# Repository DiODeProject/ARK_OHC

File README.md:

# ARK - Overhead Controller of Sheffield Robotics

Here we provide the Eagle files (schematics, layouts and gerbers) for the implementation of the new Overhead Controller (OHC) for the Kilobots. 

The bootloader for the microcontroller (Atmega328, 16MHZ) is the same as the Arduino Pro Mini and can be found here: https://github.com/arduino/Arduino/tree/master/hardware/arduino/avr/bootloaders/atmega 

The software for the microcontroller can be found here: https://github.com/acornejo/kilolib. 
Because we use 6 IR LED boards instead of 1, in file `ohc.c` we need to change line 33 to `#define ir_mask 0b00111111 | PORTB`. And then compile on the terminal as `make arduino-ohc-16mhz`.

## Citation
If you make use of or extend this design please cite:

* Nikolaidis, E., Sabo, C., Marshall, J. A. R., Reina, A. (2017) Characterisation and upgrade of the communication between overhead controllers and Kilobots. doi: [10.15131/shef.data.4990910.v2](https://figshare.com/articles/Characterisation_and_upgrade_of_the_communication_between_overhead_controllers_and_Kilobots/4990910)

## See Also
* [KilobotArena](https://github.com/DiODeProject/KilobotArena)
* [Kilobot Wiki](http://diode.group.shef.ac.uk/kilobots/index.php/Kilobots)

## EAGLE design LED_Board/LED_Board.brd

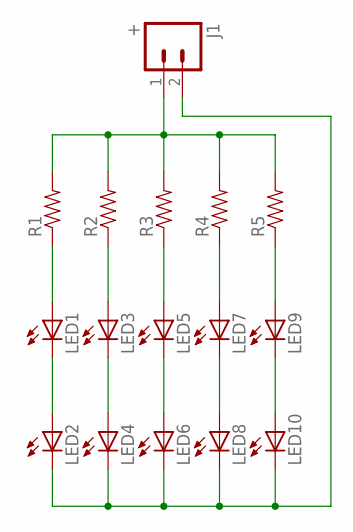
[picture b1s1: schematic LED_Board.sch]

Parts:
J1: +; 1X02_LOCK
LED1, LED2, LED3, LED4, LED5, LED6, LED7, LED8, LED9, LED10: LED5MM
R1, R2, R3, R4, R5: RESISTOR1206; 1206

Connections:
GND: J1.2, LED2.K (C), LED4.K (C), LED6.K (C), LED8.K (C), LED10.K (C)
unnamed: J1.1, R1.2, R2.2, R3.2, R4.2, R5.2
unnamed: LED9.A, R5.1
unnamed: LED7.A, R4.1
unnamed: LED5.A, R3.1
unnamed: LED3.A, R2.1
unnamed: LED1.A, R1.1
unnamed: LED1.K (C), LED2.A
unnamed: LED3.K (C), LED4.A
unnamed: LED5.K (C), LED6.A
unnamed: LED7.K (C), LED8.A
unnamed: LED9.K (C), LED10.A

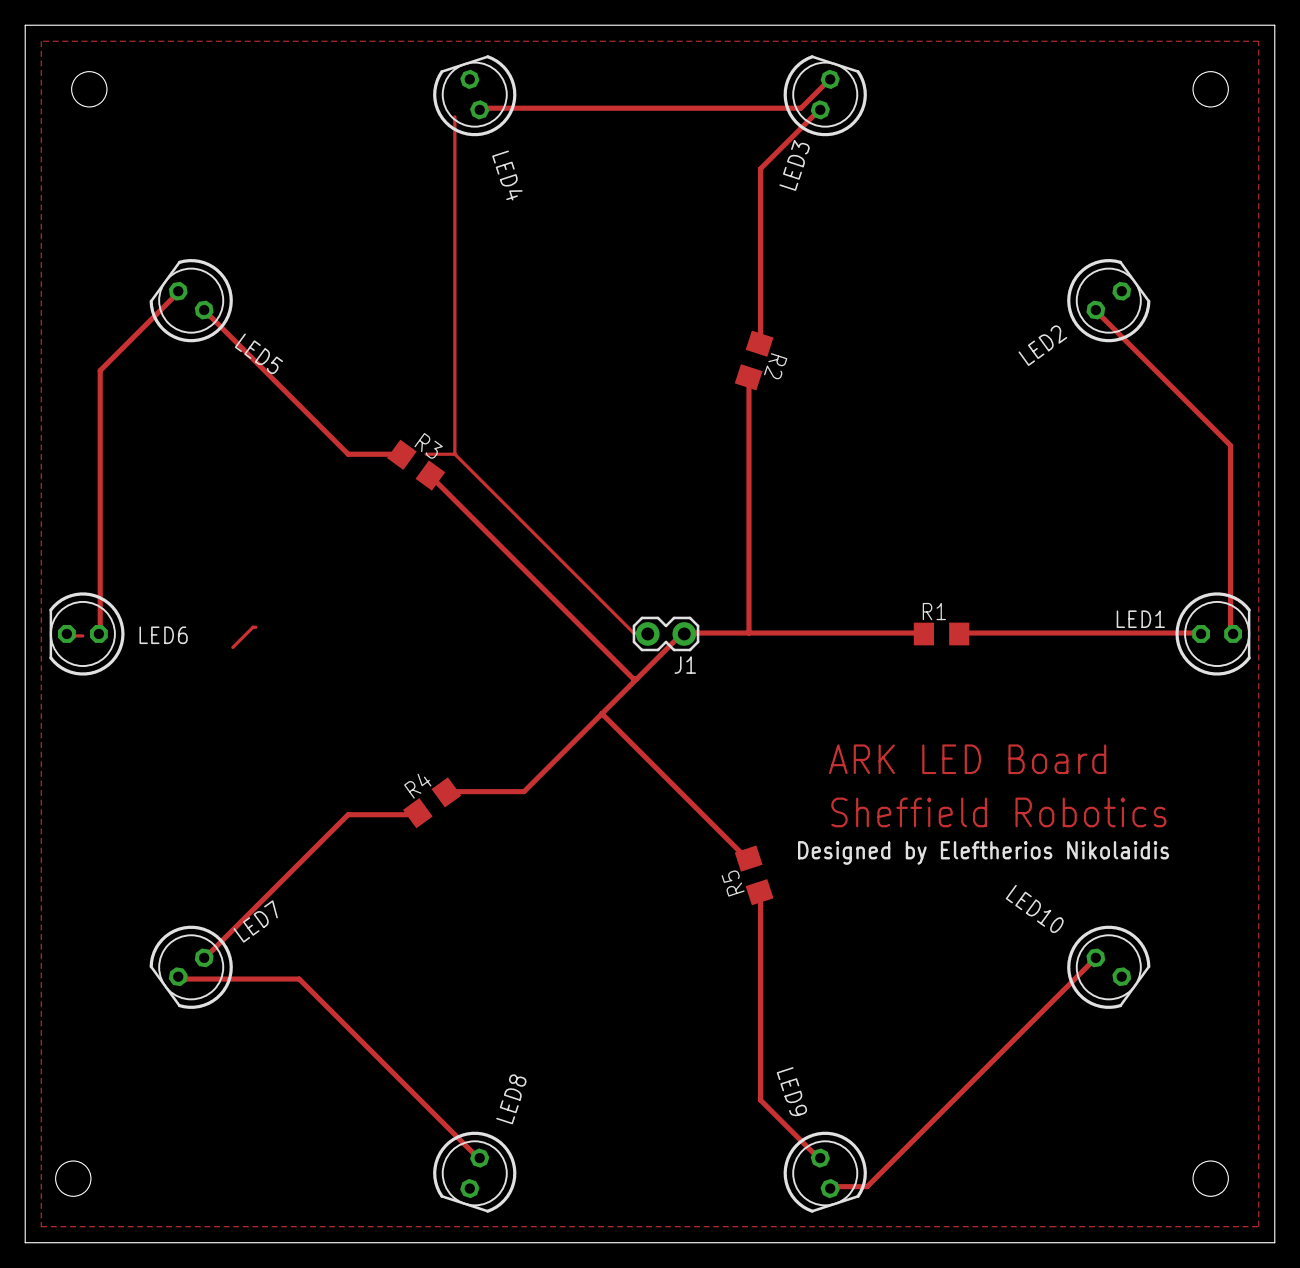
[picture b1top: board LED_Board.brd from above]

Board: 2 copper layers, 99.1 x 96.5 mm, 16 parts (0 on the bottom side), 12 nets.

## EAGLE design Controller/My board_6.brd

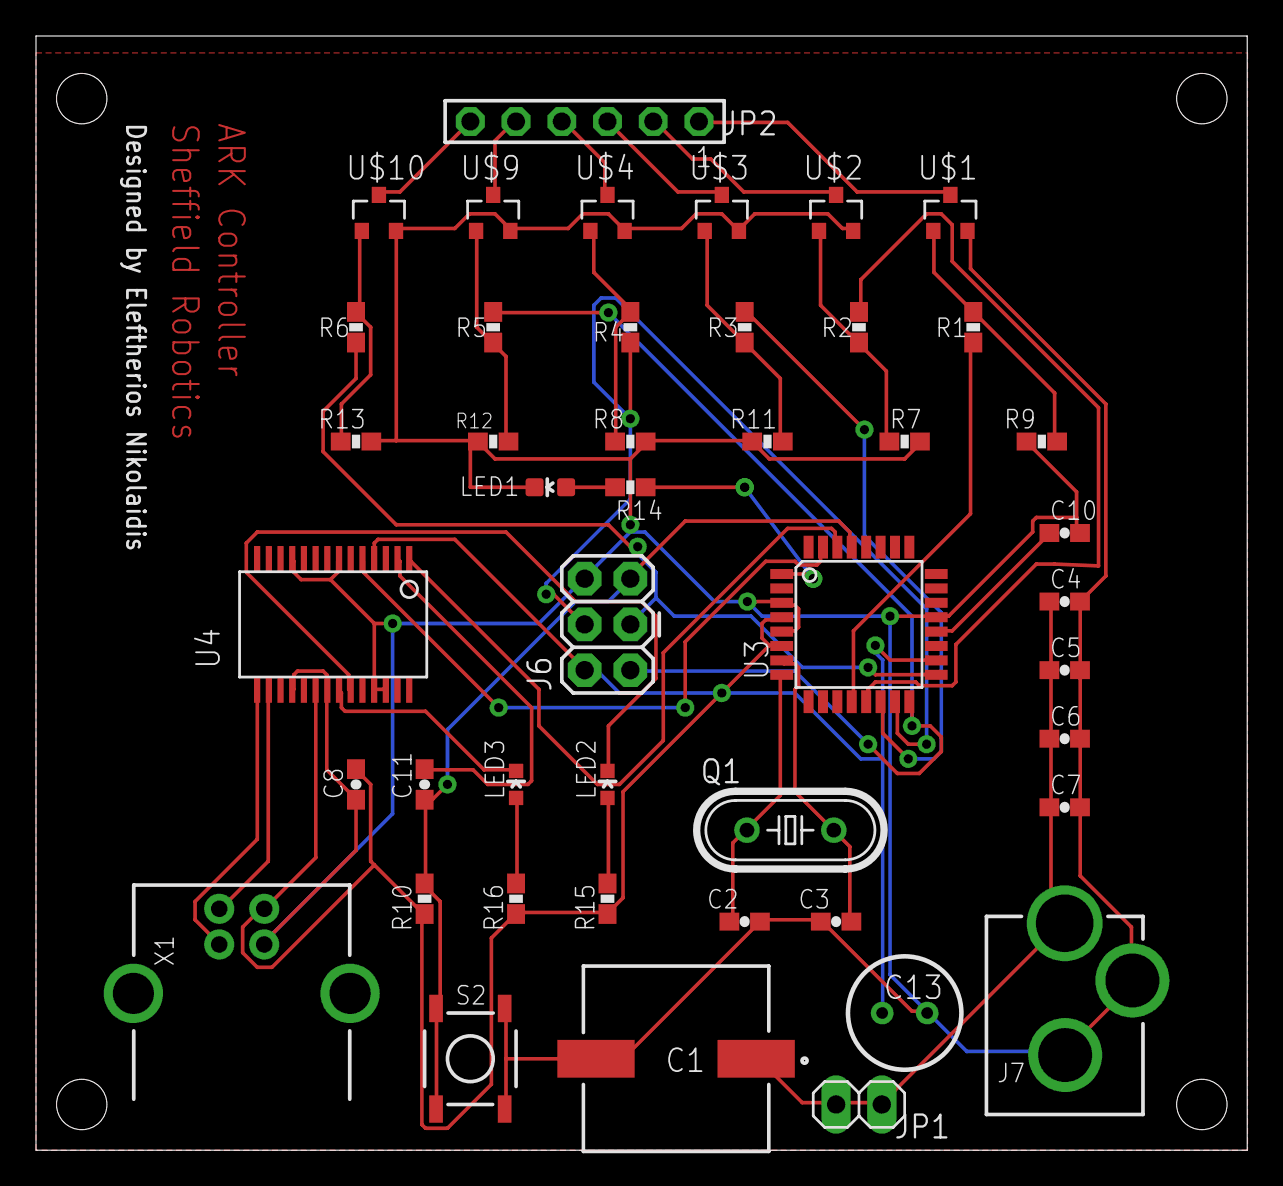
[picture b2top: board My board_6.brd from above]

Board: 2 copper layers, 67.3 x 61.9 mm, 45 parts (0 on the bottom side), 36 nets.

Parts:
C1: EEEFK1E471P; ALUMINUM-ELECTROLYTIC-CAPACITO
C2, C3: 22pf; 0603-CAP
C4, C5, C6, C7, C8, C10, C11: 0.1uF; 0603-CAP
C13: 10uF; ECEA1HKS100B
J6: ICSP; 2X3
J7: POWER_JACK; POWER_JACK_PTH_LOCK
JP1: 1X02
JP2: TSW-106-02-S-S
LED1, LED3: Green; LED-0603
LED2: Red; LED-0603
Q1: HC49/S
R1, R2, R3, R4, R5, R6: 100; 0603-RES
R7, R8, R9, R11, R12, R13: 47k; 0603-RES
R10: 10K; 0603-RES
R14, R15, R16: 1K; 0603-RES
S2: Reset; TACTILE-SWITCH-SMD-ALT01
U3: ATMEGA328; TQFP32-08
U4: FT232RL; SSOP28DB
U$1, U$2, U$3, U$4, U$9: SOT23-3
U$10: N-CHANNEL-MOSFETs-BSS138; SOT23-3
X1: USB-B; USB-B-PTH

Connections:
AREF: C10.2, U3.20
DTR1: C11.2, U4.2
GND: C1.2, C2.2, C3.2, C4.2, C5.2, C6.2, C7.2, C8.2, C10.1, C13.2, J6.6, J7.GND, J7.GNDBREAK, LED1.C, R7.2, R8.2, R9.2, R11.2, R12.2, R13.2, S2.1, S2.2, U3.3, U3.5, U3.21, U4.7, U4.11, U4.18, U4.21, U4.25, U4.26, U$1.2, U$2.2, U$3.2, U$4.2, U$9.2, U$10.2, X1.GND
unnamed: JP2.5, U$9.3
unnamed: JP2.6, U$10.3
unnamed: R3.2, U3.14
unnamed: R2.1, R7.1, U$2.1
unnamed: R3.1, R11.1, U$3.1
unnamed: R1.1, R9.1, U$1.1
unnamed: R4.1, R8.1, U$4.1
unnamed: R5.1, R12.1, U$9.1
unnamed: R6.1, R13.1, U$10.1
unnamed: C2.1, Q1.1, U3.8
unnamed: C3.1, Q1.2, U3.7
unnamed: LED2.A, R15.1
unnamed: LED3.A, R16.1
unnamed: U3.30, U4.1
unnamed: R1.2, U3.12
unnamed: R2.2, U3.13
unnamed: J6.4, R4.2, U3.15
unnamed: JP2.1, U$1.3
unnamed: JP2.2, U$2.3
unnamed: JP2.3, U$3.3
unnamed: JP2.4, U$4.3
unnamed: J6.1, R5.2, U3.16
unnamed: C1.1, C4.1, C5.1, C6.1, C7.1, J7.PWR, JP1.1, JP1.2
RESET: C11.1, J6.5, R10.1, S2.3, S2.4, U3.29
RXLED1: LED3.C, U4.22
S$1: U3.31, U4.5
S$4: R14.2, U3.1
S$5: LED1.A, R14.1
SCK1: J6.3, R6.2, U3.17
TXLED1: LED2.C, U4.23
USB_D+1: U4.15, X1.D+
USB_D-1: U4.16, X1.D-
VCCIO: C8.1, C13.1, J6.2, R10.2, R15.2, R16.2, U3.4, U3.6, U3.18, U4.4, U4.20, X1.VBUS

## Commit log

2017-09-20 * Added LED to the control board for indicating that the OHC is sending a command * Corrections on the silkscreen for both boards (size of the names of the components)
2018-01-29 Update README.md
    Added citation and link details - tidied up presentation

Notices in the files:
parts and their libraries:
Connectors: Licensing: Creative Commons ShareAlike 4.0 International - https://creativecommons.org/licenses/by-sa/4.0
